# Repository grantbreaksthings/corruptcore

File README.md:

# Corrupt Core
## Overview

This device induces corruptions (glitches) inside of retro videogame console hardware. It is controlled with an AVR ATMEGA328p running the Arduino bootloader and using various Arduino libraries. It is designed to run off of 5V, a voltage level that can be commonly found inside of retro videogame consoles.

## Inducing a Corruption

To create a corruption, the corrupt core forces a bus line inside of the videogame console to always read as logic low. It does this by using a darlington transistor to sink the bus line to ground. This changes the data being transmitted inside the videogame console, and corrupts the game.

## User Input

A 4x4 matrix of 16 buttons are hooked up to the AVR to allow for general purpose user input. Users will be able to program each of these buttons to perform whatever kind of corruption they want.

Pinouts are also provided for 3 potentiometers to be hooked up to the analog input pins of the AVR. This enables users to create dials that can specify different levels of corruption for various groups of bus lines.

## Connecting to the Videogame Console

28 individually addressable pins are provided to the user to connect to various bus lines inside the videogame console. 

24 of these pins are addressed through a bank of 3 serial in - parallel out shift registers, and are designed for general purpose use.

4 pins are labeled as Quick Corrupt Pins. This is to address a problem with sensitive bus lines inside the videogame console. If a bus line is held low for too long, there's a possibility that it will always induce a crash. However, if a bus line can be pulled low very quickly (for only a couple of clock cycles of the game console) it can result in a much more stable and interesting corruption. These pins are hooked directly to the AVR and implement special code in order to induce a logic low pulse as fast as possible.

## Programming the Corrupt Core

The corrupt core is currently designed to hook up to an empty Arduino programmer for programming. The TX, RX, RESET, 5V, and GND lines are plugged into the appropriate pins on the programmer, and the program can be uploaded just like a regular Arduino.

I realize this is obtuse and a little wierd, and there will be a future revision of the Corrupt Core that works like an Arduino Shield. I'm building it like this as a prototype, and because it makes the corrupt core easy to integrate into the videogame console.

## Notes
Please note, I do not have any formal training in Electrical Engineering or PCB design. If my schematic or board is terrible, do not hesistate to open an issue and let me know. I'm basically figuring all of this out as I go along.

##License Info
Corrupt Core
This device and software is designed to induce real time glitches in videogame hardware
Copyright (C) 2017 Grant 

This program is free software: you can redistribute it and/or modify it under the terms of the GNU General Public License as published by the Free Software Foundation, either version 3 of the License, or (at your option) any later version.

This program is distributed in the hope that it will be useful, but WITHOUT ANY WARRANTY; without even the implied warranty of MERCHANTABILITY or FITNESS FOR A PARTICULAR PURPOSE.  See the GNU General Public License for more details.

You should have received a copy of the GNU General Public License along with this program.  If not, see <http://www.gnu.org/licenses/>.

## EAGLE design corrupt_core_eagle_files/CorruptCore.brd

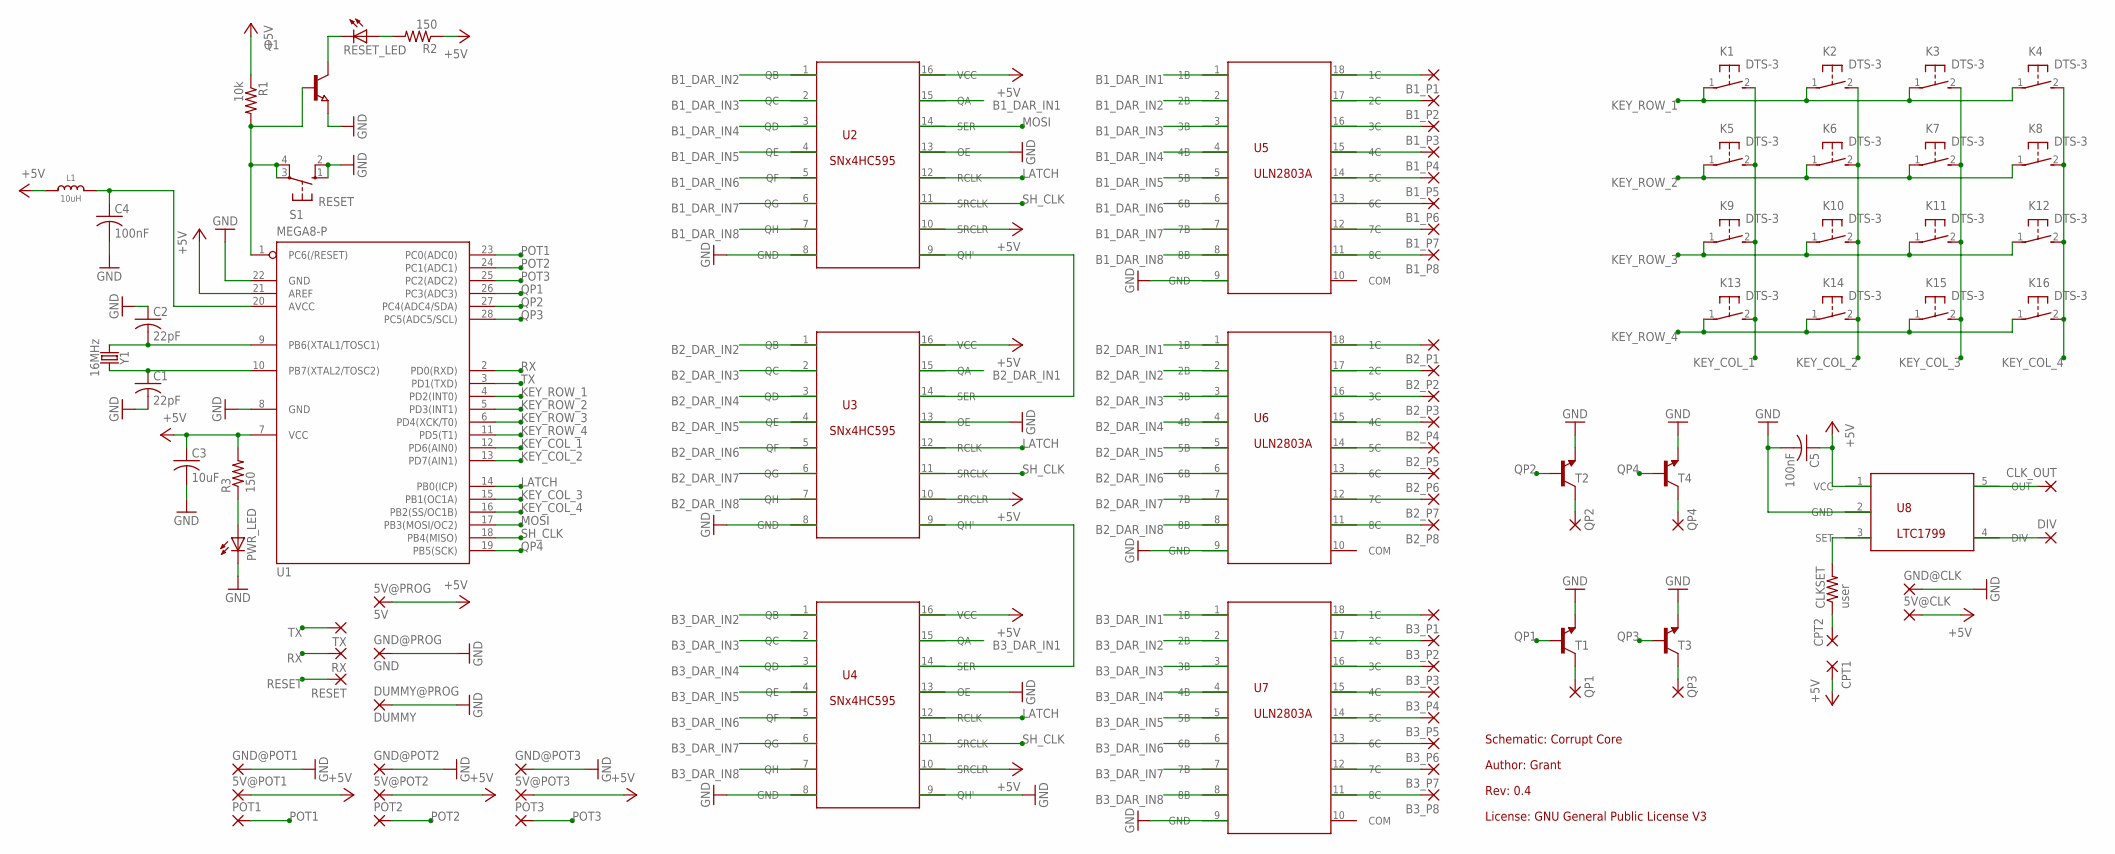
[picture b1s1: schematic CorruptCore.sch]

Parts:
5V@CLK, 5V@POT1, 5V@POT2, 5V@POT3: 1,6/0,8
5V@PROG: 5V; 1,6/0,8
B1_P1, B1_P2, B1_P3, B1_P4, B1_P5, B1_P6, B1_P7, B1_P8, B2_P1, B2_P2, B2_P3, B2_P4, B2_P5, B2_P6, B2_P7, B2_P8, B3_P1, B3_P2, B3_P3, B3_P4, B3_P5, B3_P6, B3_P7, B3_P8: 1,6/0,8
C1, C2: 22pF; C0805
C3: 10uF; C0805
C4, C5: 100nF; C0805
CLKSET: user; 0207/7
CLK_OUT: 1,6/0,8
CPT1, CPT2: 1,6/0,8
DIV: 1,6/0,8
DUMMY@PROG: DUMMY; 1,6/0,8
GND@CLK: 1,6/0,8
GND@POT1, GND@POT2, GND@POT3: 1,6/0,8
GND@PROG: GND; 1,6/0,8
K1, K2, K3, K4, K5, K6, K7, K8, K9, K10, K11, K12, K13, K14, K15, K16: DTS-3
L1: 10uH; MICROBUILDER__0805
POT1, POT2, POT3: 1,6/0,8
PWR_LED: LEDCHIPLED_0603; CHIPLED_0603
Q1: NPN-TRANSISTOR_SOT23; SOT23
QP1, QP2, QP3, QP4: 1,6/0,8
R1: 10k; R0805
R2, R3: 150; R0805
RESET: 1,6/0,8
RESET_LED: LEDCHIPLED_0603; CHIPLED_0603
RX: 1,6/0,8
S1: RESET; B3F-10XX
T1, T2, T3, T4: TRANS_NPN-MMBTA42; SOT23-3
TX: 1,6/0,8
U1: MEGA8-P; DIL28-3
U2, U3, U4: SNX4HC595SOIC16; SOIC16N
U5, U6, U7: ULN2803ASOIC18; SO18L
U8: LTC1799; SOT23-5L
Y1: 16MHz; HC49US

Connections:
+5V: 5V@CLK.1, 5V@POT1.1, 5V@POT2.1, 5V@POT3.1, 5V@PROG.1, C3.1, C5.1, CPT1.1, L1.1, R1.1, R2.1, R3.2, U1.7 (VCC), U1.21 (AREF), U2.10 (SRCLR), U2.16 (VCC), U3.10 (SRCLR), U3.16 (VCC), U4.10 (SRCLR), U4.16 (VCC), U8.1 (VCC)
B1_DAR_IN1: U2.15 (QA), U5.1 (1B)
B1_DAR_IN2: U2.1 (QB), U5.2 (2B)
B1_DAR_IN3: U2.2 (QC), U5.3 (3B)
B1_DAR_IN4: U2.3 (QD), U5.4 (4B)
B1_DAR_IN5: U2.4 (QE), U5.5 (5B)
B1_DAR_IN6: U2.5 (QF), U5.6 (6B)
B1_DAR_IN7: U2.6 (QG), U5.7 (7B)
B1_DAR_IN8: U2.7 (QH), U5.8 (8B)
B1_P1: B1_P1.1, U5.18 (1C)
B1_P2: B1_P2.1, U5.17 (2C)
B1_P3: B1_P3.1, U5.16 (3C)
B1_P4: B1_P4.1, U5.15 (4C)
B1_P5: B1_P5.1, U5.14 (5C)
B1_P6: B1_P6.1, U5.13 (6C)
B1_P7: B1_P7.1, U5.12 (7C)
B1_P8: B1_P8.1, U5.11 (8C)
B2_DAR_IN1: U3.15 (QA), U6.1 (1B)
B2_DAR_IN2: U3.1 (QB), U6.2 (2B)
B2_DAR_IN3: U3.2 (QC), U6.3 (3B)
B2_DAR_IN4: U3.3 (QD), U6.4 (4B)
B2_DAR_IN5: U3.4 (QE), U6.5 (5B)
B2_DAR_IN6: U3.5 (QF), U6.6 (6B)
B2_DAR_IN7: U3.6 (QG), U6.7 (7B)
B2_DAR_IN8: U3.7 (QH), U6.8 (8B)
B2_P1: B2_P1.1, U6.18 (1C)
B2_P2: B2_P2.1, U6.17 (2C)
B2_P3: B2_P3.1, U6.16 (3C)
B2_P4: B2_P4.1, U6.15 (4C)
B2_P5: B2_P5.1, U6.14 (5C)
B2_P6: B2_P6.1, U6.13 (6C)
B2_P7: B2_P7.1, U6.12 (7C)
B2_P8: B2_P8.1, U6.11 (8C)
B3_DAR_IN1: U4.15 (QA), U7.1 (1B)
B3_DAR_IN2: U4.1 (QB), U7.2 (2B)
B3_DAR_IN3: U4.2 (QC), U7.3 (3B)
B3_DAR_IN4: U4.3 (QD), U7.4 (4B)
B3_DAR_IN5: U4.4 (QE), U7.5 (5B)
B3_DAR_IN6: U4.5 (QF), U7.6 (6B)
B3_DAR_IN7: U4.6 (QG), U7.7 (7B)
B3_DAR_IN8: U4.7 (QH), U7.8 (8B)
B3_P1: B3_P1.1, U7.18 (1C)
B3_P2: B3_P2.1, U7.17 (2C)
B3_P3: B3_P3.1, U7.16 (3C)
B3_P4: B3_P4.1, U7.15 (4C)
B3_P5: B3_P5.1, U7.14 (5C)
B3_P6: B3_P6.1, U7.13 (6C)
B3_P7: B3_P7.1, U7.12 (7C)
B3_P8: B3_P8.1, U7.11 (8C)
GND: C1.2, C2.1, C3.2, C4.2, C5.2, DUMMY@PROG.1, GND@CLK.1, GND@POT1.1, GND@POT2.1, GND@POT3.1, GND@PROG.1, PWR_LED.C, Q1.2 (E), S1.1 (S), S1.2 (S1), T1.2 (E), T2.2 (E), T3.2 (E), T4.2 (E), U1.8 (GND), U1.22 (GND), U2.8 (GND), U2.13 (OE), U3.8 (GND), U3.13 (OE), U4.8 (GND), U4.9 (QH'), U4.13 (OE), U5.9 (GND), U6.9 (GND), U7.9 (GND), U8.2 (GND)
KEY_COL_1: K1.2, K5.2, K9.2, K13.2, U1.12 (PD6(AIN0))
KEY_COL_2: K2.2, K6.2, K10.2, K14.2, U1.13 (PD7(AIN1))
KEY_COL_3: K3.2, K7.2, K11.2, K15.2, U1.15 (PB1(OC1A))
KEY_COL_4: K4.2, K8.2, K12.2, K16.2, U1.16 (PB2(SS/OC1B))
KEY_ROW_1: K1.1, K2.1, K3.1, K4.1, U1.4 (PD2(INT0))
KEY_ROW_2: K5.1, K6.1, K7.1, K8.1, U1.5 (PD3(INT1))
KEY_ROW_3: K9.1, K10.1, K11.1, K12.1, U1.6 (PD4(XCK/T0))
KEY_ROW_4: K13.1, K14.1, K15.1, K16.1, U1.11 (PD5(T1))
LATCH: U1.14 (PB0(ICP)), U2.12 (RCLK), U3.12 (RCLK), U4.12 (RCLK)
MOSI: U1.17 (PB3(MOSI/OC2)), U2.14 (SER)
unnamed: U2.9 (QH'), U3.14 (SER)
unnamed: U3.9 (QH'), U4.14 (SER)
unnamed: C2.2, U1.9 (PB6(XTAL1/TOSC1)), Y1.1
unnamed: C1.1, U1.10 (PB7(XTAL2/TOSC2)), Y1.2
unnamed: CLK_OUT.1, U8.5 (OUT)
unnamed: R2.2, RESET_LED.A
unnamed: PWR_LED.A, R3.1
unnamed: QP1.1, T1.3 (C)
unnamed: C4.1, L1.2, U1.20 (AVCC)
unnamed: QP2.1, T2.3 (C)
unnamed: QP3.1, T3.3 (C)
unnamed: QP4.1, T4.3 (C)
unnamed: DIV.1, U8.4 (DIV)
unnamed: CLKSET.1, CPT2.1
unnamed: CLKSET.2, U8.3 (SET)
unnamed: Q1.3 (C), RESET_LED.C
POT1: POT1.1, U1.23 (PC0(ADC0))
POT2: POT2.1, U1.24 (PC1(ADC1))
POT3: POT3.1, U1.25 (PC2(ADC2))
QP1: T1.1 (B), U1.26 (PC3(ADC3))
QP2: T2.1 (B), U1.27 (PC4(ADC4/SDA))
QP3: T3.1 (B), U1.28 (PC5(ADC5/SCL))
QP4: T4.1 (B), U1.19 (PB5(SCK))
RESET: Q1.1 (B), R1.2, RESET.1, S1.3, S1.4 (P1), U1.1 (PC6(/RESET))
RX: RX.1, U1.2 (PD0(RXD))
SH_CLK: U1.18 (PB4(MISO)), U2.11 (SRCLK), U3.11 (SRCLK), U4.11 (SRCLK)
TX: TX.1, U1.3 (PD1(TXD))

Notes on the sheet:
Schematic: Corrupt Core
Author: Grant
Rev: 0.4
License: GNU General Public License V3

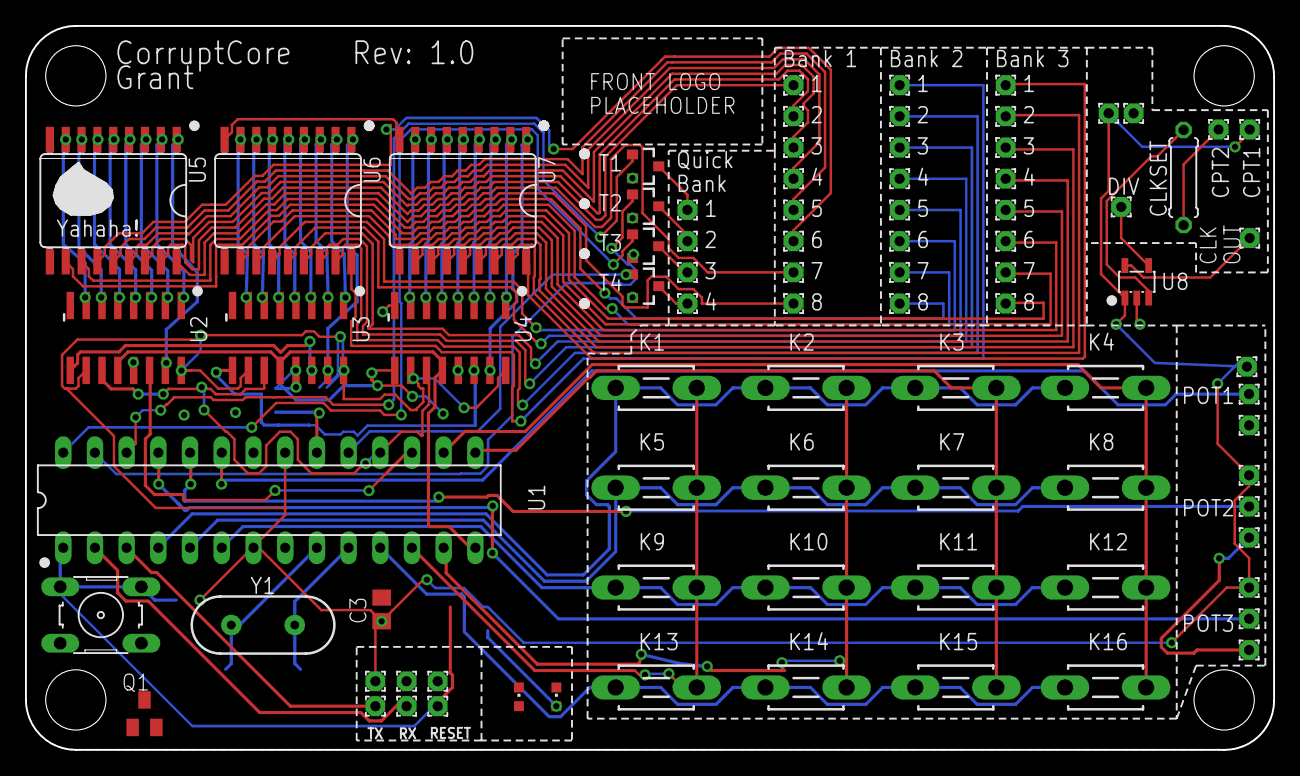
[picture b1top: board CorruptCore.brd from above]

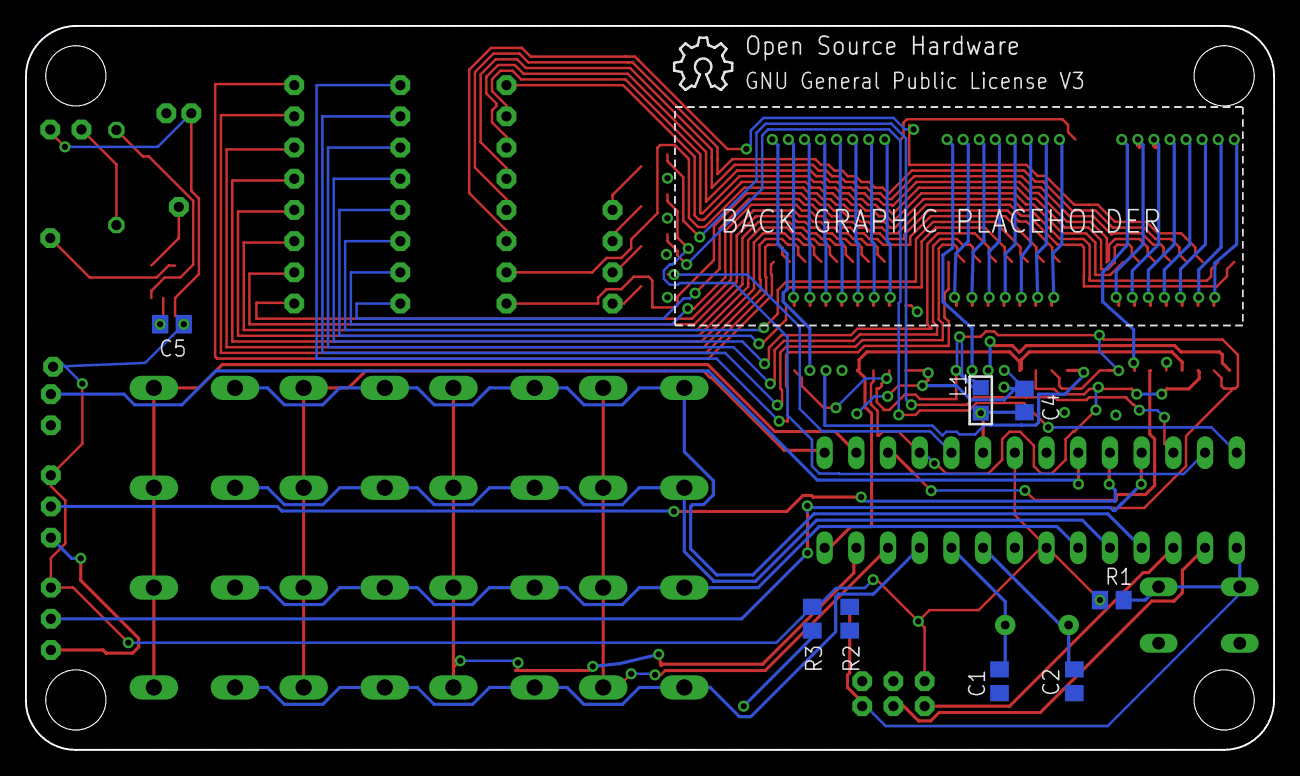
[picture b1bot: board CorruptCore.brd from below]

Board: 2 copper layers, 100.0 x 58.0 mm, 92 parts (8 on the bottom side), 87 nets.

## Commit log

2017-08-27 -first commit
2017-08-28 -fixed library dependecies
2017-08-28 -renamed pins -cleaned up schematic -added another SR/Darlington bank
2017-08-28 -designed keypad schematic -added LEDs to schematic
2017-08-28 -removed diodes from the keypad, they would have broken it. Replaced them with jumpers. It's a hack, but it will make laying things out on the board easier. I will remove them eventually -Added pinou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
2017-08-28 -added various line filters for cleaner signals -cleaned up schematic -added license terms
2017-08-28 -forgot to include darlington transistors for the quick corrupt pins
2017-08-28 -added a PNG of the schematic -small amounts of schematic cleaning
2017-08-28 -file organization
2017-08-28 -fixed the keypad wirings
2017-08-28 -added smt package variants for the shift register and darlington array
2017-08-28 -started laying out board -further organized schematic
2017-08-28 -more board changes
2017-08-28 -added LTC1799 device to library -added LTC1799 to the schematic -added LTC1799 to the board -small board/schematic cleanup
2017-08-28 -board cleanups
2017-08-29 -added graphics placeholders
2017-08-29 -added placeholders for graphics
2017-08-29 -added open source hardware logo
2017-08-29 -added shitty meme
2017-08-29 -starting to fix up the soldermask
2017-08-30 -more silkscreen changes
2017-08-30 -made the shitty meme worse
2017-08-30 -added dimensions -added DRC for Elecrow boardhouse -pretty much done with silkscreen
2017-08-30 -added a CSV BOM from DigiKey (I wanted to use mouser but they don't carry the LTC1799) -updated the schematic image
2017-08-30 Create LICENSE

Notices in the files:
eagle_files/CorruptCore.sch:
License: Creative Commons Attribution-ShareAlike
CC BY-SA
parts and their libraries:
SparkFun-Clocks: Licensing: Creative Commons ShareAlike 4.0 International - https://creativecommons.org/licenses/by-sa/4.0
